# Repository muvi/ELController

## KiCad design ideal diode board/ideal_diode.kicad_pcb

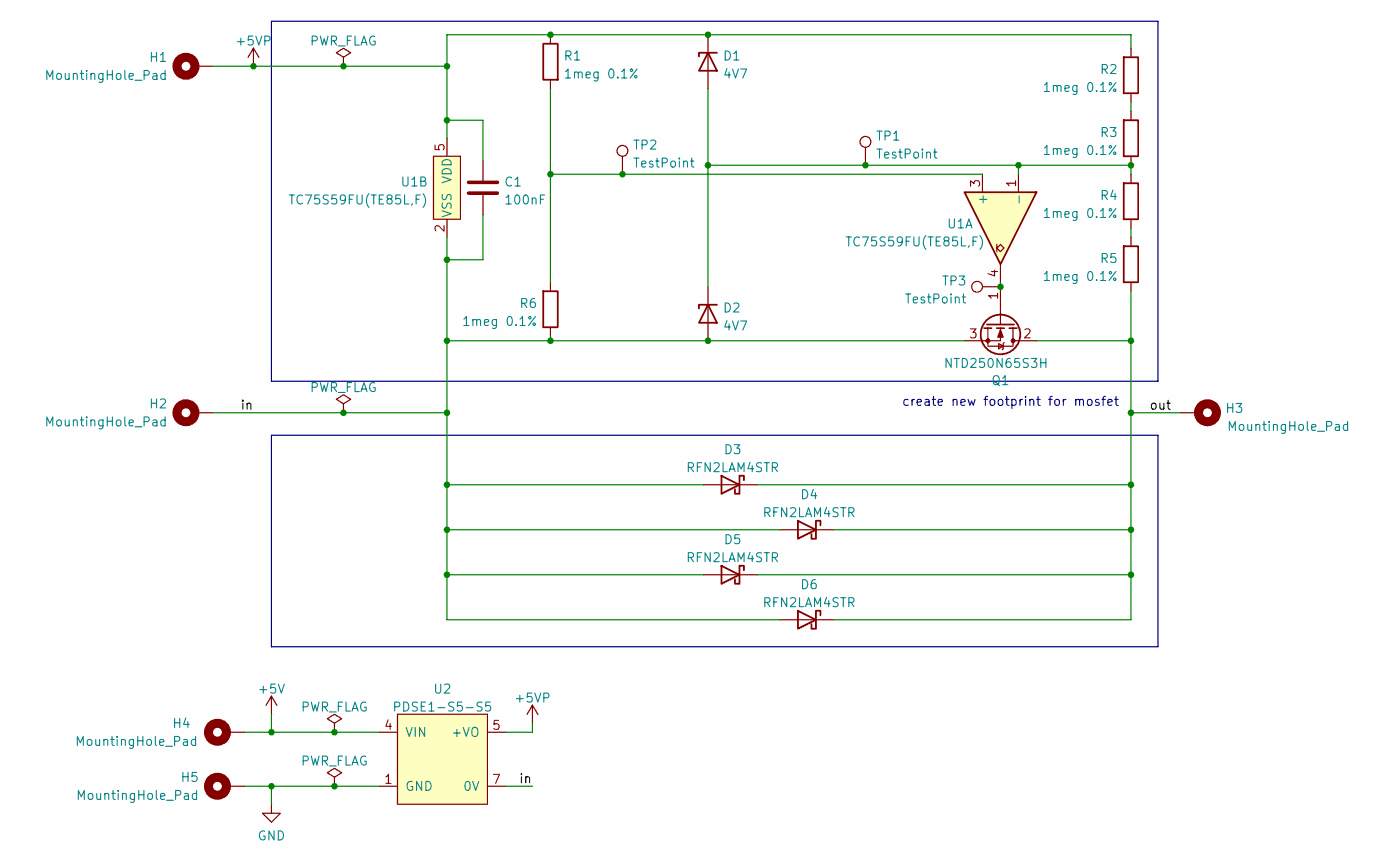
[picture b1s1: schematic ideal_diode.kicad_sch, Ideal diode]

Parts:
C1: 100nF; C_0603_1608Metric
D1, D2: 4V7; SOT-23
D3, D4, D5, D6: RFN2LAM4STR; D_SOD-128
H1, H2, H3, H4, H5: MountingHole_Pad; MountingHole_3.2mm_M3_Pad_Via
Q1: NTD250N65S3H; TO-252 3 LD
R1, R2, R3, R4, R5, R6: 1meg 0.1%; R_1206_3216Metric
TP1, TP2, TP3: TestPoint; TestPoint_THTPad_D2.0mm_Drill1.0mm
U1: TC75S59FU(TE85L,F); SSOP-P-0.95
U2: PDSE1-S5-S5; DIP-8_W7.62mm_S5-S5-D

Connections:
+5V: H4.1, U2.4 (VIN)
+5VP: C1.1, D1.3 (K), H1.1, R1.1, R2.2, U1.5 (VDD), U2.5 (+VO)
/in: C1.2, D2.1 (A), D3.2 (A), D4.2 (A), D5.2 (A), D6.2 (A), H2.1, Q1.3 (S), R6.1, U1.2 (VSS), U2.7 (0V)
/out: D3.1 (K), D4.1 (K), D5.1 (K), D6.1 (K), H3.1, Q1.2 (D), R5.1
GND: H5.1, U2.1 (GND)
unnamed: D1.1 (A), D2.3 (K), R3.1, R4.2, TP1.1, U1.1 (-)
unnamed: Q1.1 (G), TP3.1, U1.4
unnamed: R1.2, R6.2, TP2.1, U1.3 (+)
unnamed: R2.1, R3.2
unnamed: R4.1, R5.2

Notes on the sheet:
create new footprint for mosfet

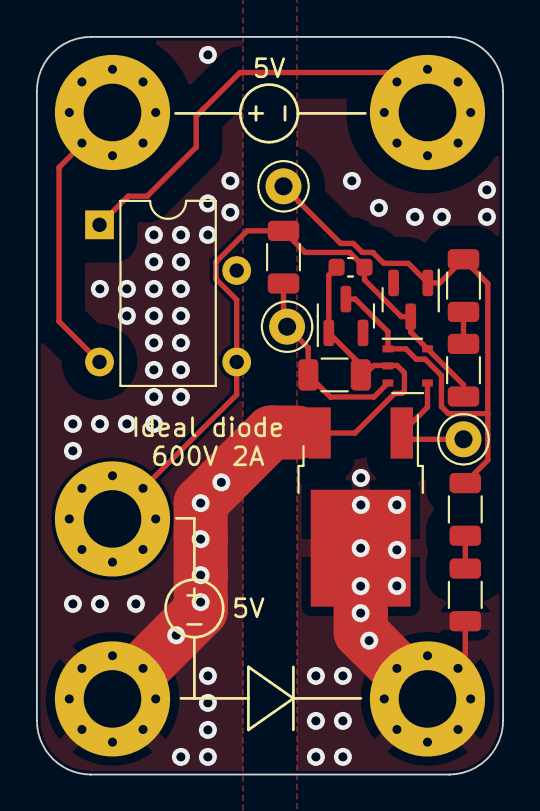
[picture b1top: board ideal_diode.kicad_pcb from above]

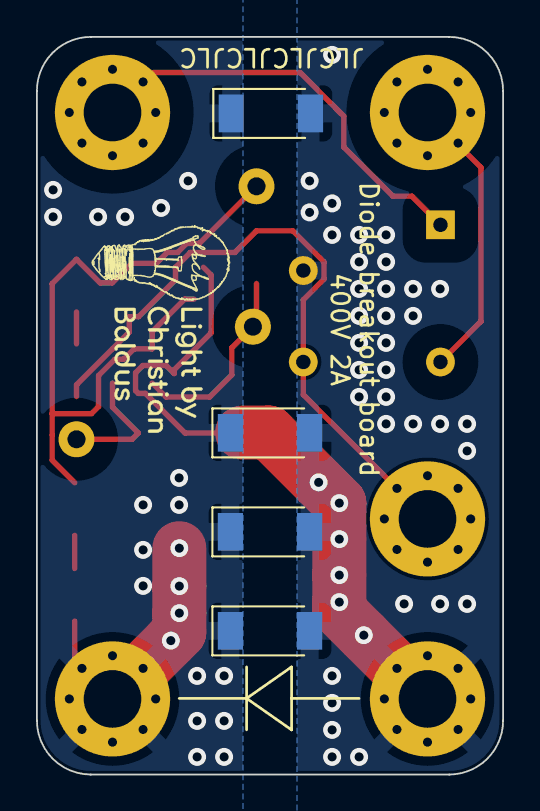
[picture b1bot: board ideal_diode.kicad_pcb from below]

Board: 4 copper layers, 25.9 x 41.0 mm, 24 parts (4 on the bottom side), 10 nets.

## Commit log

2023-07-12 - added some inventory management SQLs - testing, mesuring and repairing (changes in inventory management)
2023-07-12 removed backup files and logs
2024-01-28 Updated inventory management
